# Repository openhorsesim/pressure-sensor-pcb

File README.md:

# pressure-sensor-pcb
Impedance Reduction Circuit for Low-Cost Pressure Sensor

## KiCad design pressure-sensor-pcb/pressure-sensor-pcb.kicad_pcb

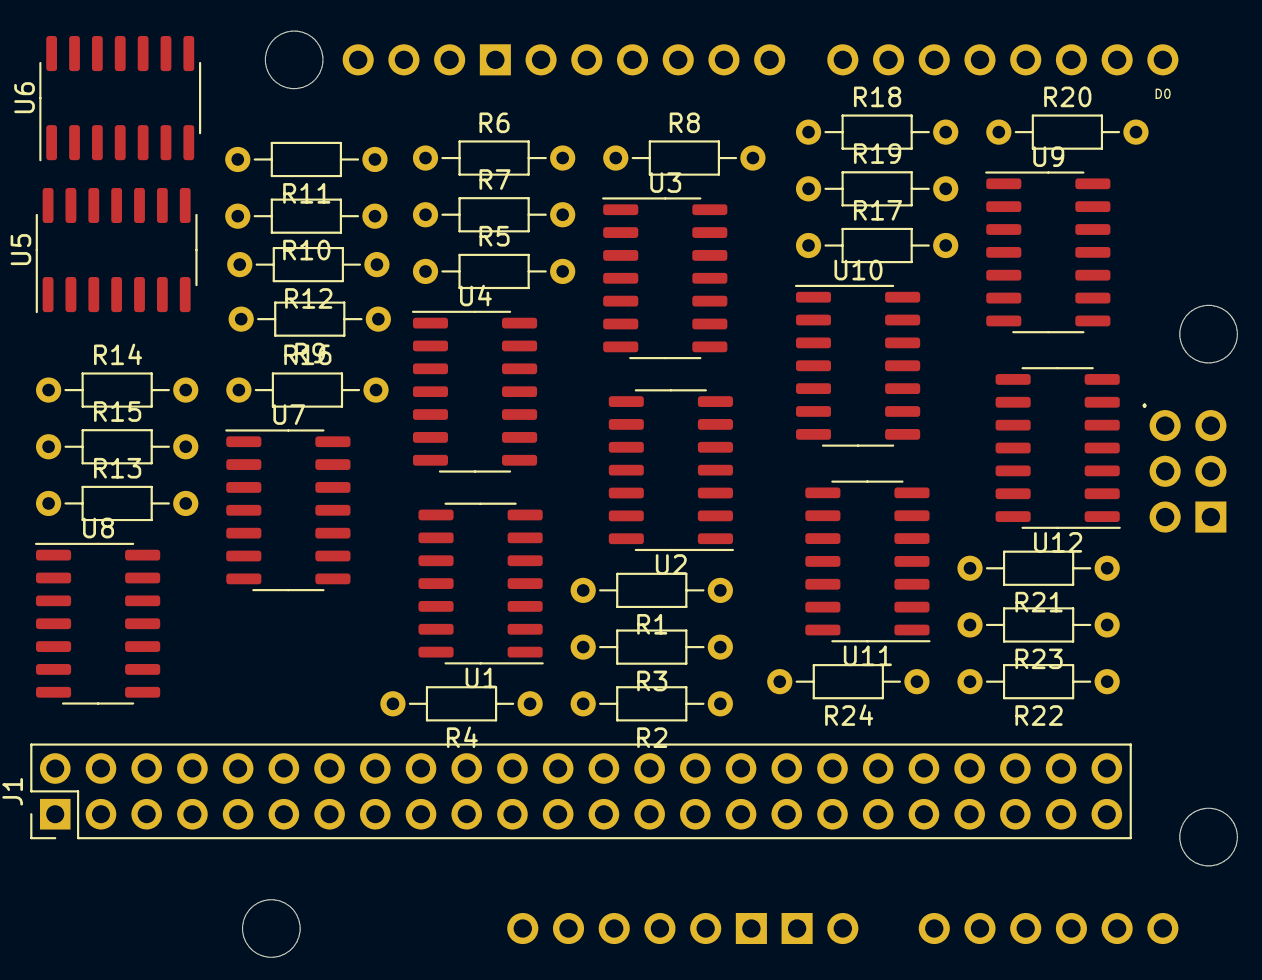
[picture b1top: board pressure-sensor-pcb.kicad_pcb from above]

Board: 2 copper layers, 38 parts (0 on the bottom side), 64 nets, no tracks yet.

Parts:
J1: Conn_02x24_Odd_Even; PinHeader_2x24_P2.54mm_Vertical
R1, R5, R9, R13, R17, R21: 10M; R_Axial_DIN0204_L3.6mm_D1.6mm_P7.62mm_Horizontal
R2, R6, R10, R14, R18, R22: 1M; R_Axial_DIN0204_L3.6mm_D1.6mm_P7.62mm_Horizontal
R3, R7, R11, R15, R19, R23: 100K; R_Axial_DIN0204_L3.6mm_D1.6mm_P7.62mm_Horizontal
R4, R8, R12, R16, R20, R24: 10K; R_Axial_DIN0204_L3.6mm_D1.6mm_P7.62mm_Horizontal
U1, U2, U3, U4, U5, U6, U7, U8, U9, U10, U11, U12: 4066; SO-14_3.9x8.65mm_P1.27mm
XA1: Arduino_Uno_WiFi_R2_Shield; Arduino_Uno_Shield

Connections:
+3V3: R1.1, R2.1, R3.1, R4.1, R5.1, R6.1, R7.1, R8.1, R9.1, R10.1, R11.1, R12.1, R13.1, R14.1, R15.1, R16.1, R17.1, R18.1, R19.1, R20.1, R21.1, R22.1, R23.1, R24.1, U1.14 (VDD), U2.14 (VDD), U3.14 (VDD), U4.14 (VDD), U5.14 (VDD), U6.14 (VDD), U7.14 (VDD), U8.14 (VDD), U9.14 (VDD), U10.14 (VDD), U11.14 (VDD), U12.14 (VDD), XA1.3V3 (3.3V)
/TAP0: U1.2, U1.3, U1.9, U1.10, U2.1, U2.4, U2.8, U2.11, XA1.A0
/TAP1: U3.2, U3.3, U3.9, U3.10, U4.1, U4.4, U4.8, U4.11, XA1.A1
/TAP2: U5.2, U5.3, U5.9, U5.10, U6.1, U6.4, U6.8, U6.11, XA1.A2
/TAP3: U7.2, U7.3, U7.9, U7.10, U8.1, U8.4, U8.8, U8.11, XA1.A3
/TAP4: U9.2, U9.3, U9.9, U9.10, U10.1, U10.4, U10.8, U10.11, XA1.A4
/TAP5: U11.2, U11.3, U11.9, U11.10, U12.1, U12.4, U12.8, U12.11, XA1.A5
/TOP1: J1.1, U2.2
/TOP2: J1.3, U2.3
/TOP3: J1.5, U2.9
/TOP4: J1.7, U2.10
/TOP5: J1.9, U4.2
/TOP6: J1.11, U4.3
/TOP7: J1.13, U4.9
/TOP8: J1.15, U4.10
/TOP9: J1.17, U6.2
/TOP10: J1.19, U6.3
/TOP11: J1.21, U6.9
/TOP12: J1.23, U6.10
/TOP13: J1.25, U8.2
/TOP14: J1.27, U8.3
/TOP15: J1.29, U8.9
/TOP16: J1.31, U8.10
/TOP17: J1.33, U10.2
/TOP18: J1.35, U10.3
/TOP19: J1.37, U10.9
/TOP20: J1.39, U10.10
/TOP21: J1.41, U12.2
/TOP22: J1.43, U12.3
/TOP23: J1.45, U12.9
/TOP24: J1.47, U12.10
GND: J1.2, J1.4, J1.6, J1.8, J1.10, J1.12, J1.14, J1.16, J1.18, J1.20, J1.22, J1.24, J1.26, J1.28, J1.30, J1.32, J1.34, J1.36, J1.38, J1.40, J1.42, J1.44, J1.46, J1.48, U1.7 (VSS), U2.7 (VSS), U3.7 (VSS), U4.7 (VSS), U5.7 (VSS), U6.7 (VSS), U7.7 (VSS), U8.7 (VSS), U9.7 (VSS), U10.7 (VSS), U11.7 (VSS), U12.7 (VSS), XA1.GND1 (GND), XA1.GND2 (GND), XA1.GND3 (GND)
unnamed: R1.2, U1.1
unnamed: R2.2, U1.4
unnamed: R3.2, U1.8
unnamed: R4.2, U1.11
unnamed: R5.2, U3.1
unnamed: R6.2, U3.4
unnamed: R7.2, U3.8
unnamed: R8.2, U3.11
unnamed: R9.2, U5.1
unnamed: R10.2, U5.4
unnamed: R11.2, U5.8
unnamed: R12.2, U5.11
unnamed: R13.2, U7.1
unnamed: R14.2, U7.4
unnamed: R15.2, U7.8
unnamed: R16.2, U7.11
unnamed: R17.2, U9.1
unnamed: R18.2, U9.4
unnamed: R19.2, U9.8
unnamed: R20.2, U9.11
unnamed: R21.2, U11.1
unnamed: R22.2, U11.4
unnamed: R23.2, U11.8
unnamed: R24.2, U11.11
RSEL1: U1.13, U3.13, U5.13, U7.13, U9.13, U11.13, XA1.D4
RSEL2: U1.5, U3.5, U5.5, U7.5, U9.5, U11.5, XA1.D5
RSEL3: U1.6, U3.6, U5.6, U7.6, U9.6, U11.6, XA1.D6
RSEL4: U1.12, U3.12, U5.12, U7.12, U9.12, U11.12, XA1.D7
SENSEL1: U2.13, U4.13, U6.13, U8.13, U10.13, U12.13, XA1.D8
SENSEL2: U2.5, U4.5, U6.5, U8.5, U10.5, U12.5, XA1.D9
SENSEL3: U2.6, U4.6, U6.6, U8.6, U10.6, U12.6, XA1.D10 (D10_CS)
SENSEL4: U2.12, U4.12, U6.12, U8.12, U10.12, U12.12, XA1.D11

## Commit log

2023-02-24 begin designing PCB
2023-02-24 add footprints
2023-02-24 test initial PCB layout for fit
